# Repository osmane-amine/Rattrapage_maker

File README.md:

# Rattrapage_maker

L'objectif est de réaliser un PCB et un modèle 3D du chassis d'un robot auto-équilibré à 2 roues, de type Segway.

Par manque de temps, le routage du PCB et le chassis sont inachevés, cependant le schématic ainsi que l'assignation des empreintes sont terminées.

L'alimentation est gérée par une cellule de batterie LiPo, et un convertisseur boost.

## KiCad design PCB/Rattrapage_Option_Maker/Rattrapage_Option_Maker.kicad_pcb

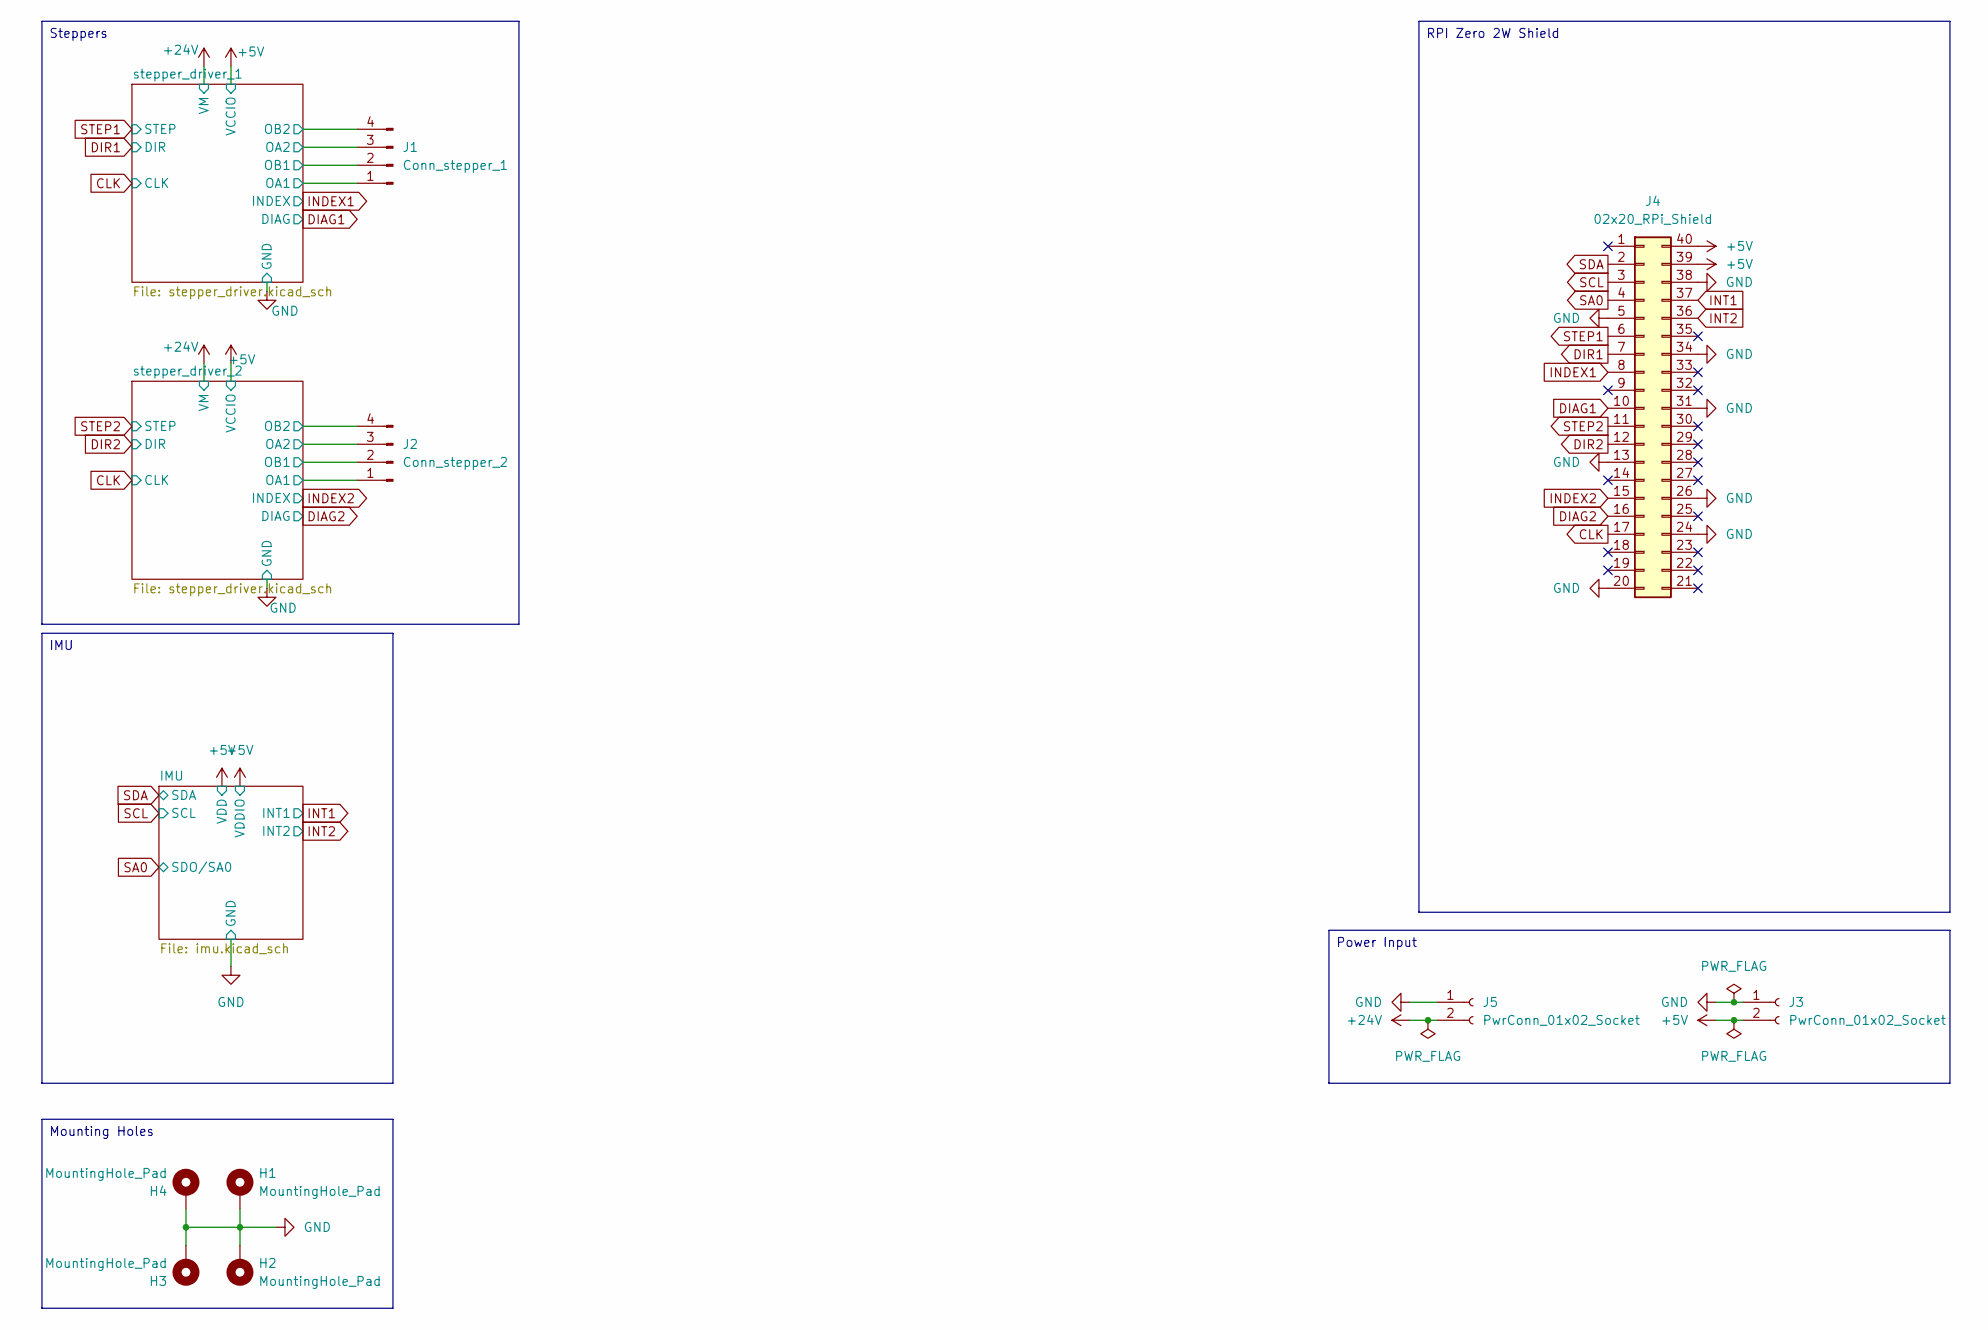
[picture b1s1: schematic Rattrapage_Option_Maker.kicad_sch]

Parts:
H1, H2, H3, H4: MountingHole_Pad; MountingHole_2.5mm_Pad
J1: Conn_stepper_1; Harwin_M20-89004xx_1x04_P2.54mm_Horizontal
J2: Conn_stepper_2; Harwin_M20-89004xx_1x04_P2.54mm_Horizontal
J3, J5: PwrConn_01x02_Socket; Molex_KK-396_A-41792-0002_1x02_P3.96mm_Horizontal
J4: 02x20_RPi_Shield; PinHeader_2x20_P2.54mm_Vertical

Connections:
+5V: J3.2, J4.39, J4.40; also elsewhere on the board
+24V: J5.2; also elsewhere on the board
/stepper_driver_1/OA1: J1.1; also elsewhere on the board
/stepper_driver_1/OA2: J1.3; also elsewhere on the board
/stepper_driver_1/OB1: J1.2; also elsewhere on the board
/stepper_driver_1/OB2: J1.4; also elsewhere on the board
/stepper_driver_2/OA1: J2.1; also elsewhere on the board
/stepper_driver_2/OA2: J2.3; also elsewhere on the board
/stepper_driver_2/OB1: J2.2; also elsewhere on the board
/stepper_driver_2/OB2: J2.4; also elsewhere on the board
CLK: J4.17; also elsewhere on the board
DIAG1: J4.10; also elsewhere on the board
DIAG2: J4.16; also elsewhere on the board
DIR1: J4.7; also elsewhere on the board
DIR2: J4.12; also elsewhere on the board
GND: H1.1, H2.1, H3.1, H4.1, J3.1, J4.5, J4.13, J4.20, J4.24, J4.26, J4.31, J4.34, J4.38, J5.1; also elsewhere on the board
INDEX1: J4.8; also elsewhere on the board
INDEX2: J4.15; also elsewhere on the board
INT1: J4.37; also elsewhere on the board
INT2: J4.36; also elsewhere on the board
SA0: J4.4; also elsewhere on the board
SCL: J4.3; also elsewhere on the board
SDA: J4.2; also elsewhere on the board
STEP1: J4.6; also elsewhere on the board
STEP2: J4.11; also elsewhere on the board

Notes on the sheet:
Mounting Holes
RPI Zero 2W Shield
Steppers
IMU
Power Input

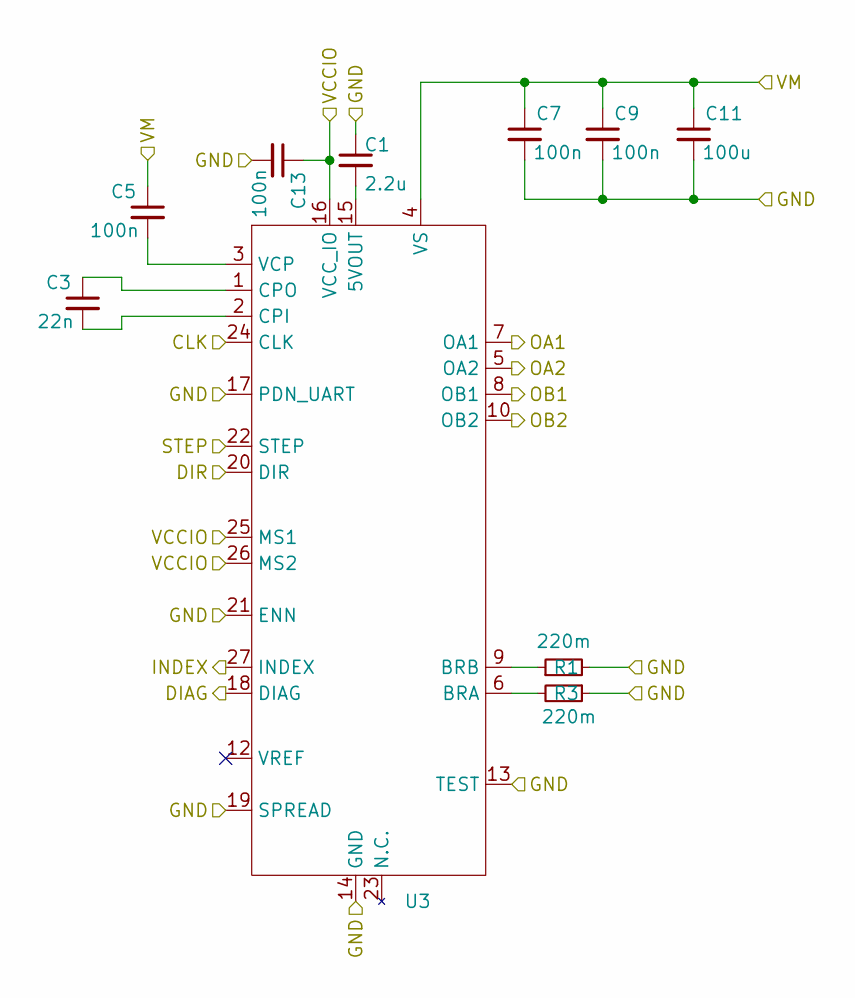
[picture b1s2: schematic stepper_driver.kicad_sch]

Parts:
C1: 2.2u; C_0504_1310Metric
C3: 22n; C_0504_1310Metric
C5, C7, C9, C13: 100n; C_0504_1310Metric
C11: 100u; C_0504_1310Metric
R1, R3: 220m; R_0603_1608Metric_Pad0.98x0.95mm_HandSolder
U3: HTSSOP-28-1EP_4.4x9.7mm_P0.65mm_EP2.75x6.2mm

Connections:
+5V: C13.1, U3.16 (VCC_IO), U3.25 (MS1), U3.26 (MS2); also elsewhere on the board
+24V: C5.1, C7.1, C9.1, C11.1, U3.4 (VS), U3.11 (VS); also elsewhere on the board
/stepper_driver_1/OA1: U3.7 (OA1); also elsewhere on the board
/stepper_driver_1/OA2: U3.5 (OA2); also elsewhere on the board
/stepper_driver_1/OB1: U3.8 (OB1); also elsewhere on the board
/stepper_driver_1/OB2: U3.10 (OB2); also elsewhere on the board
CLK: U3.24 (CLK); also elsewhere on the board
DIAG1: U3.18 (DIAG); also elsewhere on the board
DIR1: U3.20 (DIR); also elsewhere on the board
GND: C1.1, C7.2, C9.2, C11.2, C13.2, R1.2, R3.1, U3.13 (TEST), U3.14 (GND), U3.17 (PDN_UART), U3.19 (SPREAD), U3.21 (ENN), U3.28 (GND), U3.29 (GND); also elsewhere on the board
INDEX1: U3.27 (INDEX); also elsewhere on the board
unnamed: C1.2, U3.15 (5VOUT)
unnamed: R3.2, U3.6 (BRA)
unnamed: R1.1, U3.9 (BRB)
unnamed: C3.2, U3.2 (CPI)
unnamed: C3.1, U3.1 (CPO)
unnamed: C5.2, U3.3 (VCP)
STEP1: U3.22 (STEP); also elsewhere on the board

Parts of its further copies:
C2: 2.2u; C_0504_1310Metric
C4: 22n; C_0504_1310Metric
C6, C8, C10, C14: 100n; C_0504_1310Metric
C12: 100u; C_0504_1310Metric
R2, R4: 220m; R_0603_1608Metric_Pad0.98x0.95mm_HandSolder
U4: HTSSOP-28-1EP_4.4x9.7mm_P0.65mm_EP2.75x6.2mm

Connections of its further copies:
+5V: C14.1, U4.16 (VCC_IO), U4.25 (MS1), U4.26 (MS2); also elsewhere on the board
+24V: C6.1, C8.1, C10.1, C12.1, U4.4 (VS), U4.11 (VS); also elsewhere on the board
/stepper_driver_2/OA1: U4.7 (OA1); also elsewhere on the board
/stepper_driver_2/OA2: U4.5 (OA2); also elsewhere on the board
/stepper_driver_2/OB1: U4.8 (OB1); also elsewhere on the board
/stepper_driver_2/OB2: U4.10 (OB2); also elsewhere on the board
CLK: U4.24 (CLK); also elsewhere on the board
DIAG2: U4.18 (DIAG); also elsewhere on the board
DIR2: U4.20 (DIR); also elsewhere on the board
GND: C2.1, C8.2, C10.2, C12.2, C14.2, R2.2, R4.1, U4.13 (TEST), U4.14 (GND), U4.17 (PDN_UART), U4.19 (SPREAD), U4.21 (ENN), U4.28 (GND), U4.29 (GND); also elsewhere on the board
INDEX2: U4.27 (INDEX); also elsewhere on the board
unnamed: C2.2, U4.15 (5VOUT)
unnamed: R4.2, U4.6 (BRA)
unnamed: R2.1, U4.9 (BRB)
unnamed: C4.2, U4.2 (CPI)
unnamed: C4.1, U4.1 (CPO)
unnamed: C6.2, U4.3 (VCP)
STEP2: U4.22 (STEP); also elsewhere on the board

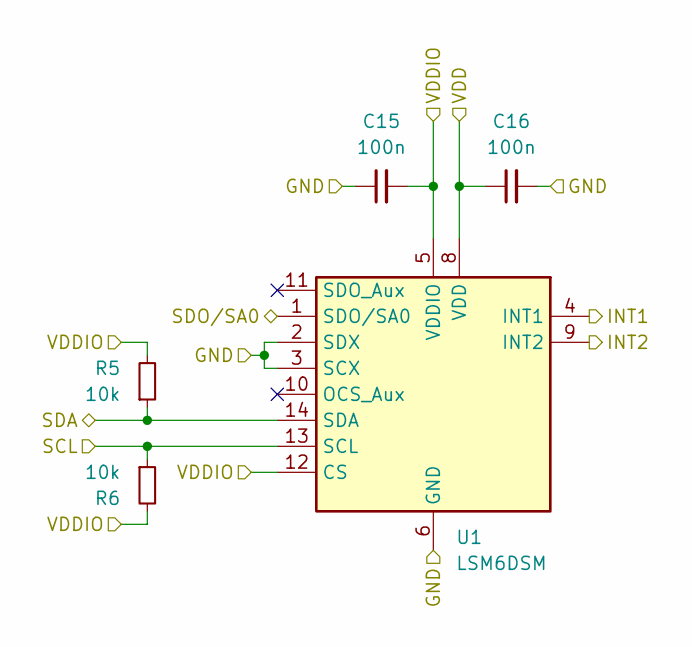
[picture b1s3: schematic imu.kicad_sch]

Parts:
C15, C16: 100n; C_0504_1310Metric
R5, R6: 10k; R_0603_1608Metric_Pad0.98x0.95mm_HandSolder
U1: LSM6DSM; LGA-14_3x2.5mm_P0.5mm_LayoutBorder3x4y

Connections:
+5V: C15.2, C16.1, R5.2, R6.2, U1.5 (VDDIO), U1.8 (VDD), U1.12 (CS); also elsewhere on the board
GND: C15.1, C16.2, U1.2 (SDX), U1.3 (SCX), U1.6 (GND), U1.7 (GND); also elsewhere on the board
INT1: U1.4 (INT1); also elsewhere on the board
INT2: U1.9 (INT2); also elsewhere on the board
SA0: U1.1 (SDO/SA0); also elsewhere on the board
SCL: R6.1, U1.13 (SCL); also elsewhere on the board
SDA: R5.1, U1.14 (SDA); also elsewhere on the board

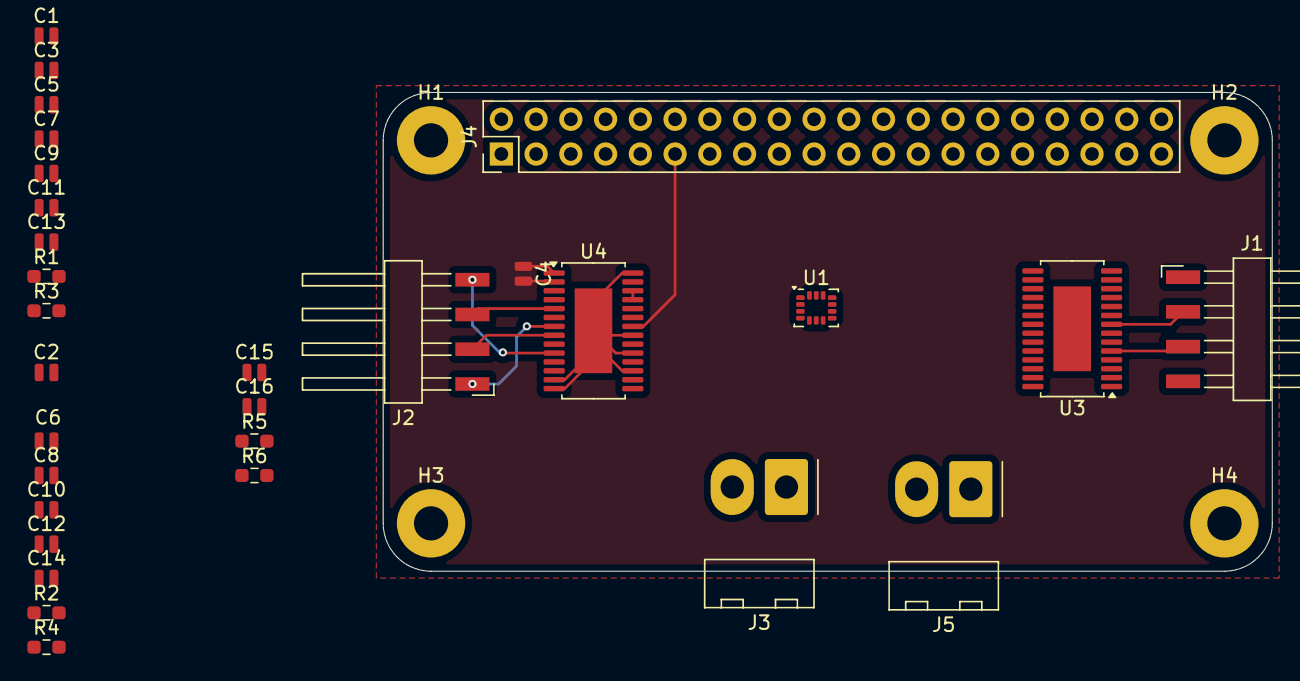
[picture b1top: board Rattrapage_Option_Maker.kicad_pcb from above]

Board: 2 copper layers, 65.0 x 35.0 mm, 34 parts (0 on the bottom side), 37 nets.
